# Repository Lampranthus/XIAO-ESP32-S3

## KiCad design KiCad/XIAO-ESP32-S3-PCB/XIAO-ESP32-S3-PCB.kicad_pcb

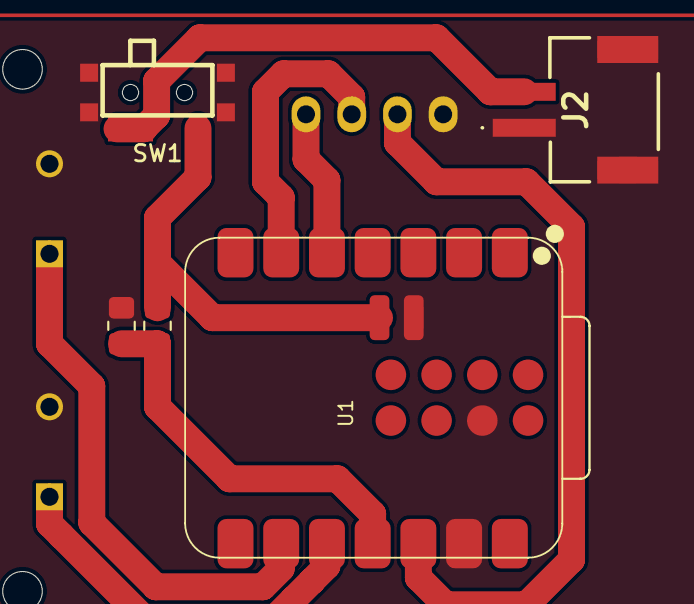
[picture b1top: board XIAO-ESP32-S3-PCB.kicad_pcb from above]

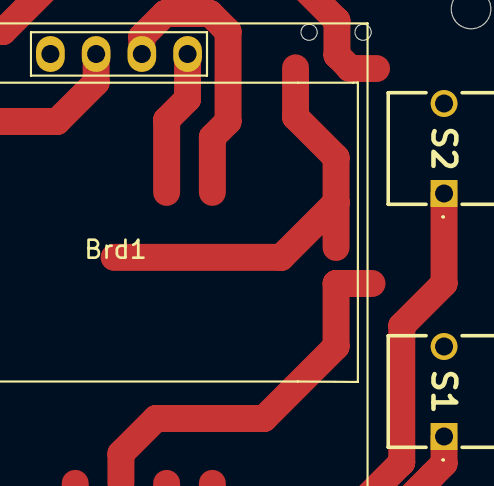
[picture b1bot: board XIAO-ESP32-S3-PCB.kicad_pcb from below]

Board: 2 copper layers, 8 parts (3 on the bottom side), 9 nets.

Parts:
Brd1: SSD1306; 128x64OLED
J2: A2001WR-S-2P_SMT; A2001WRS2PSMT
R1, R2: R; R_0805_2012Metric_Pad1.20x1.40mm_HandSolder
S1, S2: DTST-63K-V; DTST63KV
SW1: SK-3296S-01-L1; SW-SMD_3P-P1.50_L2.7-W6.6
U1: XIAO-ESP32-S3-SMD; XIAO-ESP32S3-SMD

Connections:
3V3: Brd1.2 (VCC), U1.12 (3V3)
GND: Brd1.1 (GND), J2.1, J2.3 (MP1), J2.4 (MP2), R1.2, S1.2 (NO), S2.2 (NO), SW1.0, U1.13 (GND), U1.16 (GND), U1.20 (GND)
PUSH_1: S1.1 (COM), U1.10 (GPIO8_A9_D9_MISO)
PUSH_2: S2.1 (COM), U1.9 (GPIO7_A8_D8_SCK)
SCL: Brd1.3 (SCL), U1.6 (GPIO6_A5_D5_SCL)
SDA: Brd1.4 (SDA), U1.5 (GPIO5_A4_D4_SDA)
SWITCH_DIV_V_BATT: R1.1, R2.2, U1.11 (GPIO9_A10_D10_MOSI)
SWITCH_V_BATT: R2.1, SW1.1, U1.15 (BAT)
V_BATT: J2.2, SW1.2, SW1.3

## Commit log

2025-03-28 PCB added
2025-03-29 hardware tested
